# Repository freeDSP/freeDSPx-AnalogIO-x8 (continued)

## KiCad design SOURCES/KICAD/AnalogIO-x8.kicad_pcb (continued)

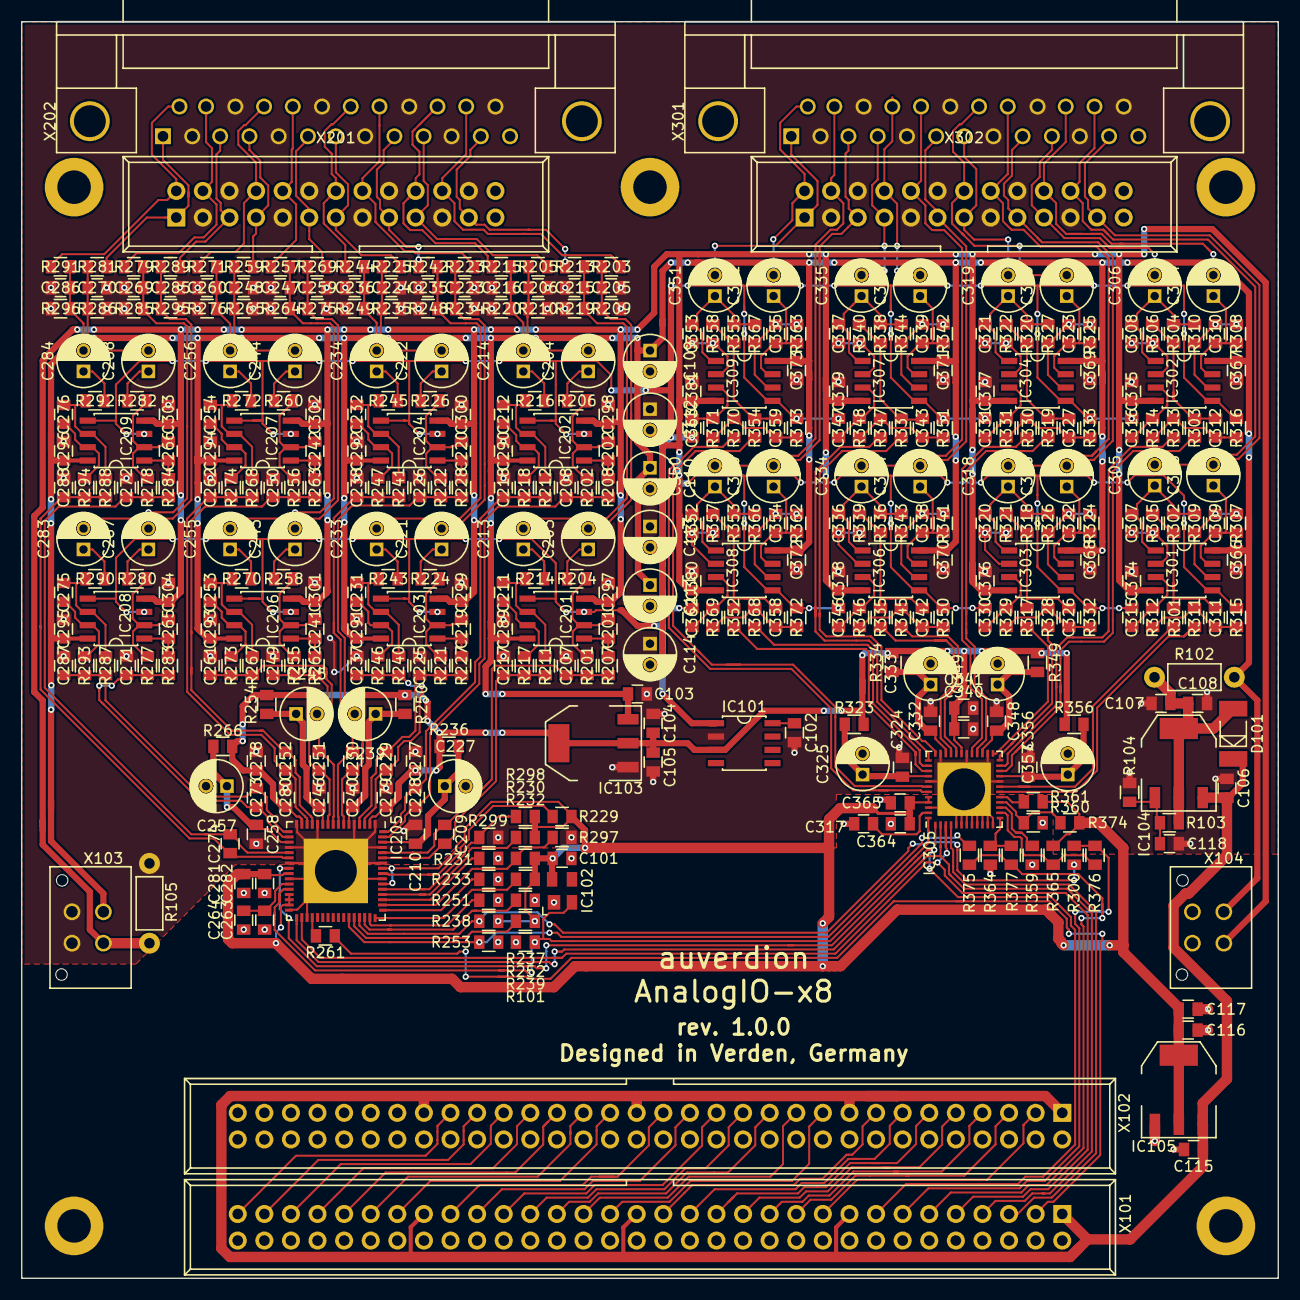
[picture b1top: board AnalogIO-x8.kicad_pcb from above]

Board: 2 copper layers, 120.0 x 120.0 mm, 418 parts (0 on the bottom side), 251 nets.

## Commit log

2018-08-09 Init
2018-08-09 Created Gerbers and BOM
2018-10-05 Added some comments to schematics
2018-10-07 Documentation
2018-10-09 Exported BOM to PDF and Excel
